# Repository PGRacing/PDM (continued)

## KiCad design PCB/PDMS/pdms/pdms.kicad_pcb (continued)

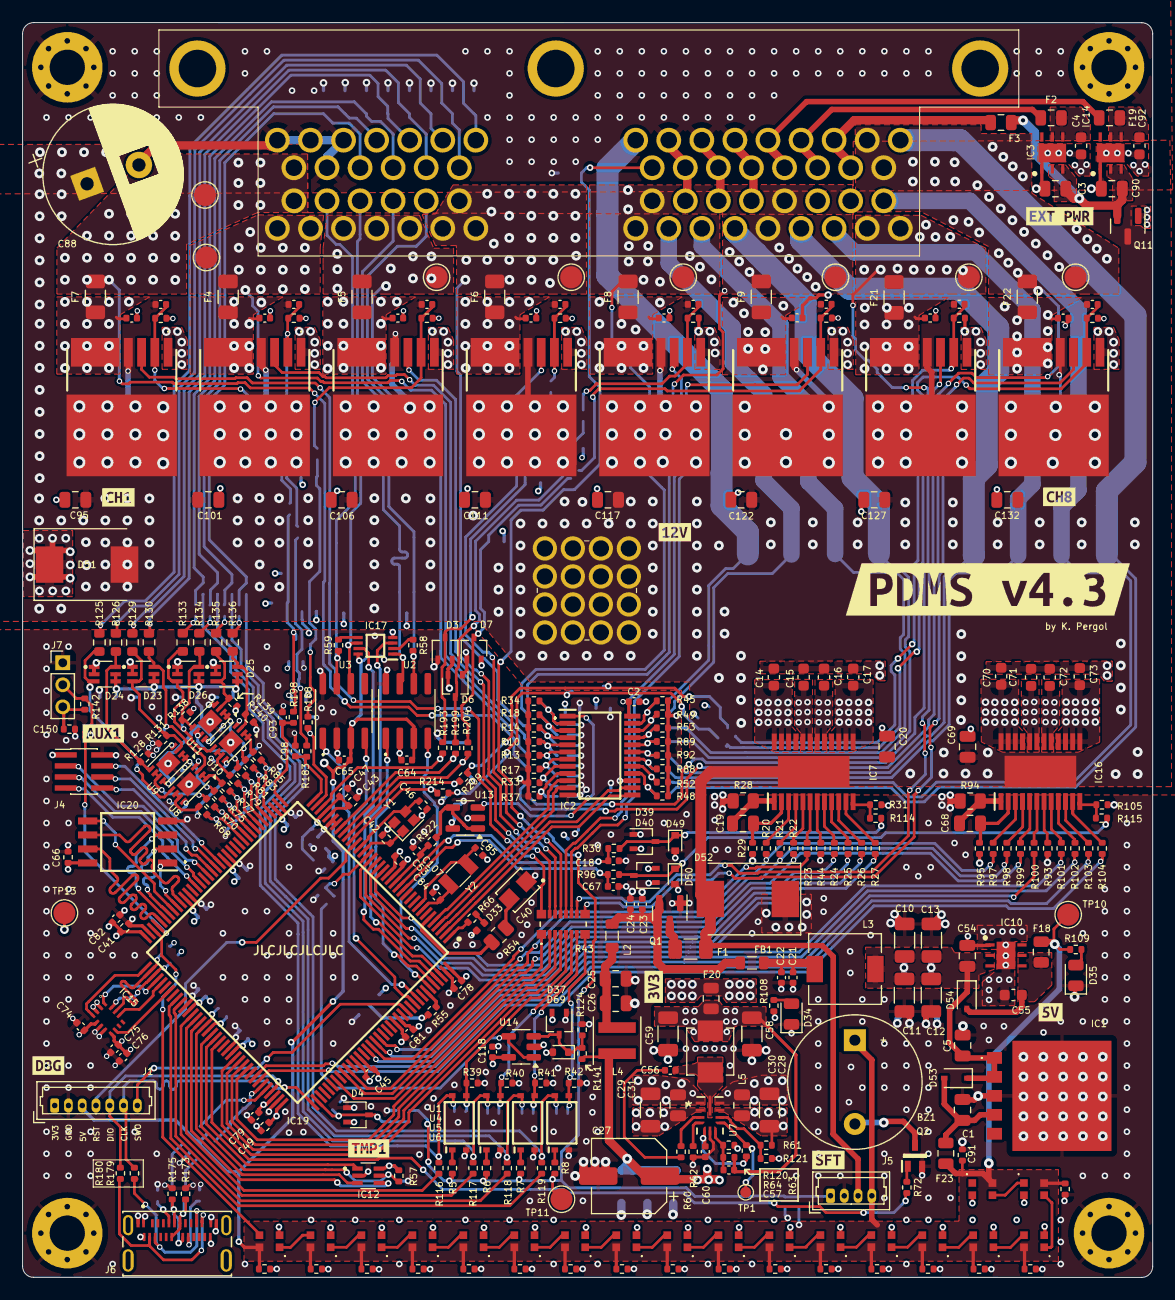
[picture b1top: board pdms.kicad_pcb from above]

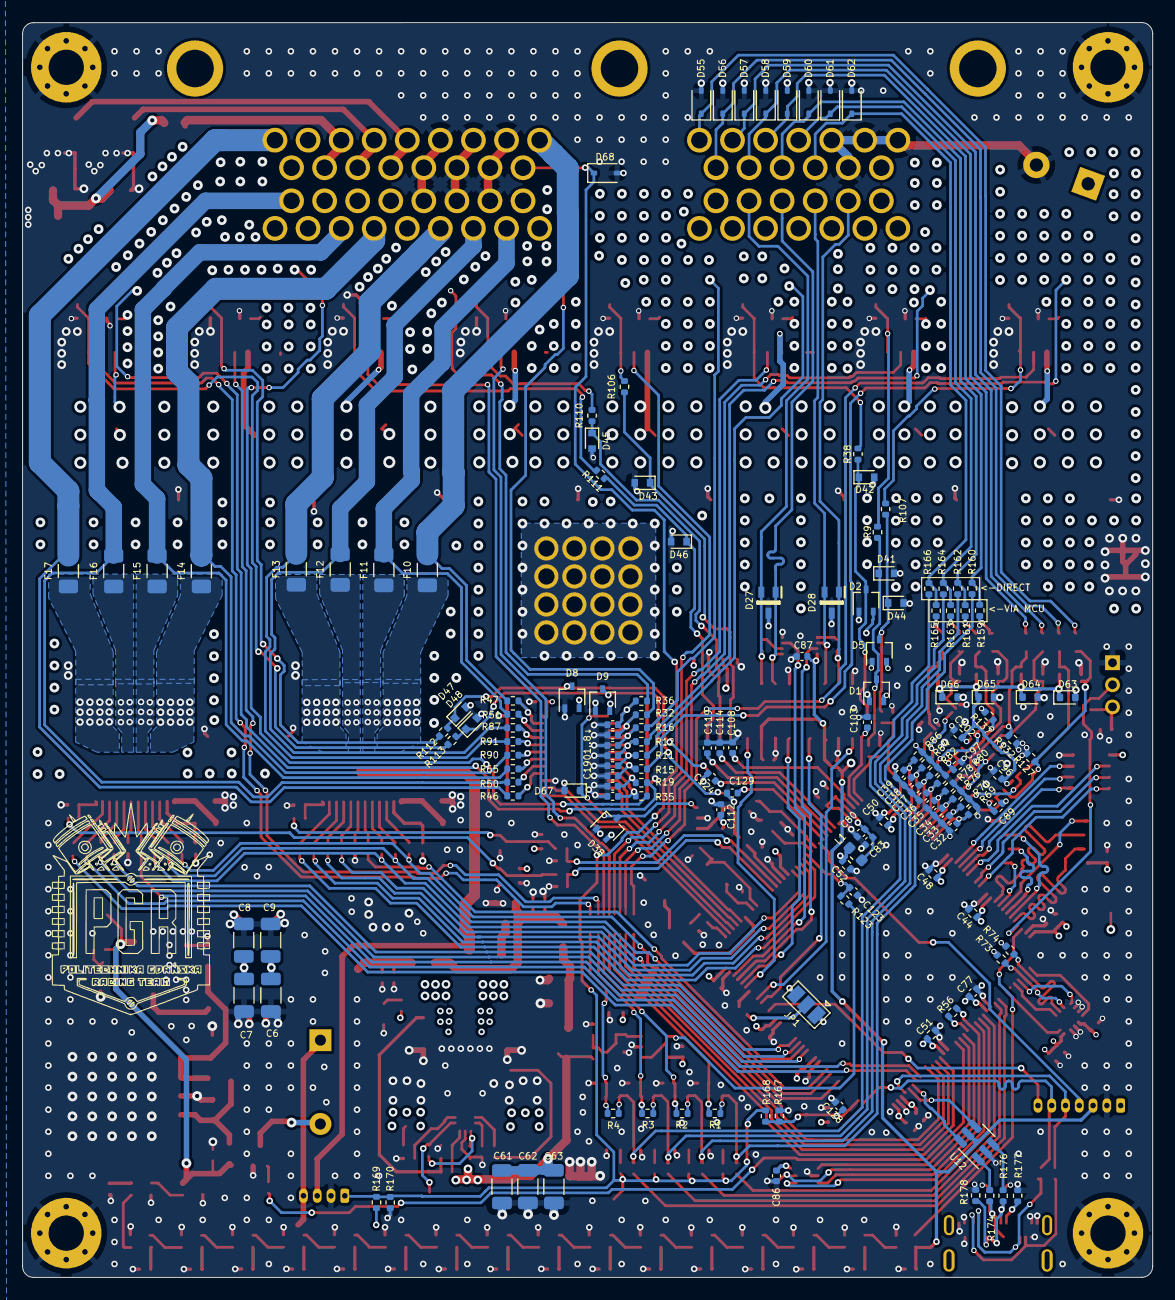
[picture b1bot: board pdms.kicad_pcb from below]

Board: 4 copper layers, 102.5 x 113.8 mm, 509 parts (147 on the bottom side), 300 nets.

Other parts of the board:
Ge: LOGO
kibuzzard-65AD9CDA: G***; kibuzzard-65AD9CDA
kibuzzard-65C2D9B8: G***; kibuzzard-65C2D9B8
kibuzzard-65C96195: G***; kibuzzard-65C96195
kibuzzard-646F7EA8: G***; kibuzzard-646F7EA8
kibuzzard-664CF65B: G***; kibuzzard-664CF65B
kibuzzard-680F5382: G***; kibuzzard-680F5382
kibuzzard-6477C3F8: G***; kibuzzard-6477C3F8
kibuzzard-64698A06: G***; kibuzzard-64698A06
kibuzzard-64713E79: G***; kibuzzard-64713E79
kibuzzard-64714FCB: G***; kibuzzard-64714FCB
kibuzzard-64716719: G***; kibuzzard-64716719

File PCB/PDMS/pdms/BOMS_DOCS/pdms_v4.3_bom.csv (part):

"Reference";"Value";"Datasheet";"Footprint";"Qty";"DNP"
"BZ1";"Buzzer";"~";"Buzzer_Beeper:Buzzer_12x9.5RM7.6";"1";""
"C1,C4,C28,C29,C55,C92";"4.7uF";"~";"-- mixed values --";"6";""
"C2,C20,C44,C45,C47,C48,C49,C50,C51,C52,C53,C64,C65,C66,C69,C74,C76,C77,C78,C79,C80,C81,C82,C86,C87,C89,C91,C95,C96,C97,C101,C102,C106,C111,C112,C117,C118,C122,C127,C132,C133,C134,C135,C136,C137,C138,C139,C140,C141,C142,C143,C144,C145,C146,C147,C148,C149,C150";"100nF";"~";"-- mixed values --";"58";""
"C3,C5,C43,C54,C60,C83,C90";"1uF";"~";"-- mixed values --";"7";""
"C6,C7,C8,C9,C10,C11,C12,C13";"10uF";"~";"Capacitor_SMD:C_1206_3216Metric";"8";""
"C14,C15,C16,C17,C24,C70,C71,C72,C73,C75,C93,C94,C98,C100,C103,C105,C108,C110,C114,C116,C119,C121,C124,C126,C129,C131";"10nF";"~";"-- mixed values --";"26";""
"C18,C67";"220pF";"~";"Capacitor_SMD:C_0402_1005Metric";"2";""
"C19,C68";"470nF";"~";"Capacitor_SMD:C_0805_2012Metric";"2";""
"C21";"100pF/50V";"~";"Capacitor_SMD:C_0402_1005Metric";"1";""
"C22";"100nF/50V";"~";"Capacitor_SMD:C_0402_1005Metric";"1";""
"C23,C99,C104,C109,C113,C115,C120,C125,C130";"1nF";"~";"Capacitor_SMD:C_0402_1005Metric";"9";""
"C25,C26";"2.2uF";"~";"Capacitor_SMD:C_0805_2012Metric";"2";""
"C27,C58,C59";"22uF";"~";"-- mixed values --";"3";""
"C30,C31";"0.1uF";"~";"Capacitor_SMD:C_0805_2012Metric";"2";""
"C32,C33,C34,C35,C36,C37,C38,C39,C56";"47nF";"~";"Capacitor_SMD:C_0402_1005Metric";"9";""
"C40";"1F";"~";"PDMS_Additional:CAPCP3225X100N";"1";""
"C41";"4u7";"~";"Resistor_SMD:R_0402_1005Metric";"1";""
"C42,C46,C57,C84,C85";"10pF";"~";"-- mixed values --";"5";""
"C61,C62";"10uF";"~";"Capacitor_SMD:C_1206_3216Metric";"2";"DNP"
"C63";"2.2uF";"~";"Capacitor_SMD:C_1206_3216Metric";"1";"DNP"
"C88";"1000uF";"~";"Capacitor_THT:CP_Radial_D12.5mm_P5.00mm";"1";""
"C107,C123,C128,R122,R123";"NA";"~";"-- mixed values --";"5";""
"D1,D2,D3,D4,D5,D6,D7,D8,D9,D37,D38,D39,D40";"BAT54SW";"https://assets.nexperia.com/documents/data-sheet/BAT54W_SER.pdf";"Package_TO_SOT_SMD:SOT-323_SC-70";"13";""
"D10,D11,D12,D13,D14,D15,D16,D17,D18,D19,D20,D21,D22,D29,D30,D31,D32,D36";"WS2812B-2020";"";"PDMS_Additional:WS2812B2020";"18";""
"D23,D24,D25,D26";"BAT54BRW-7-F";"";"PDM_Additional:SOT65P210X110-6N";"4";""
"D27,D28";"PESD2CANFD24L-UX";"https://assets.nexperia.com/documents/data-sheet/PESD2CANFD2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";"PDMS_Additional:SOT65P210X110-3N";"2";""
"D33,D34,D35";"LED";"~";"-- mixed values --";"3";""
"D41,D42,D43,D44,D45,D46,D47,D48,D49,D50,D67,D69";"SZMM5Z3V9";"SZMM5Z3V3T1G ";"Diode_SMD:D_SOD-523";"12";""
"D51";"SMC_TVS_28V";"~";"Diode_SMD:D_SMC";"1";""
"D52";"D_TVS";"~";"Diode_SMD:D_SMC";"1";""
"D53,D54";"1N4448WS";"https://www.vishay.com/docs/81387/1n4448ws.pdf";"Diode_SMD:D_SOD-323";"2";""
"D55,D56,D57,D58,D59,D60,D61,D62";"TSD05";"~";"Diode_SMD:D_SOD-323";"8";""
"D63,D64,D65,D66";"SZMM5Z5V3";"~";"Diode_SMD:D_SOD-523";"4";""
"D68";"12V";"~";"Diode_SMD:D_SOD-323";"1";""
"F1,F20";"2A";"~";"-- mixed values --";"2";""
"F2,F18,F19,F23";"100mA";"~";"Fuse:Fuse_0805_2012Metric";"4";""
"F3";"3A";"~";"Fuse:Fuse_0805_2012Metric";"1";""
"F4,F5,F6,F7,F8,F9,F21,F22";"Fuse";"~";"Fuse:Fuse_1206_3216Metric";"8";""
"F10,F11,F12,F13,F14,F15,F16,F17";"7A";"~";"Fuse:Fuse_1206_3216Metric";"8";""
"FB1,L2";"742792063";"~";"Inductor_SMD:L_0805_2012Metric";"2";""
"H1,H2,H3,H4";"MountingHole_Pad";"~";"MountingHole:MountingHole_3.2mm_M3_Pad_Via";"4";""
"IC1";"BD50FD0WHFP-TR";"";"PDMS_Additional:BD50FD0WHFPTR";"1";""
"IC2";"74HC4067PW-Q100J";"";"PDMS_Additional:SOP65P640X110-24N";"1";""
"IC3";"LDO40LPU33RY";"";"PDMS_Additional:SON95P300X300X90-7N-D";"1";""
"IC7,IC16";"BTS722204ESAXUMA1";"https://www.infineon.com/dgdl/Infineon-BTS72220-4ESA-DS-v01_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";"PDMS_Additional:SOP65P600X115-25N";"2";""
"IC10,IC14";"LDO40LPU50RY";"https://componentsearchengine.com/Datasheets/1/LDO40LPU50RY.pdf";"PDMS_Additional:SON95P300X300X90-7N-D";"2";""
"IC12";"TMP126NDCKR";"https://www.ti.com/lit/ds/symlink/tmp126.pdf";"PDM_Additional:SOT65P210X110-6N";"1";""
"IC15";"ASM330LHHTR";"https://www.st.com/resource/en/datasheet/asm330lhh.pdf";"PDMS_Additional:LGA-14_2.5X3X0.86_";"1";""
"IC17";"TS5A21366DCUR";"https://datasheet.datasheetarchive.com/originals/distributor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";"PDM_Additional:SOP50P310X90-8N";"1";""
"IC19";"STM32L496ZGT6";"https://componentsearchengine.com/Datasheets/2/STM32L496ZGT6.pdf";"PDM_Additional:QFP50P2200X2200X160-144N";"1";""
"IC20";"AT25SF128A-SHB-T";"https://www.dialog-semiconductor.com/sites/default/files/202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";"PDM_Additional:SOIC127P798X216-8N";"1";""
"J1";"DBG";"~";"Connector_Molex:Molex_PicoBlade_53047-0710_1x07_P1.25mm_Vertical";"1";""
"J2";"6473427-1";"https://www.te.com/commerce/DocumentDelivery/DDEController?A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";"PDMS_Additional:64734271";"1";""
"J3";"7461383";"";"PDMS_Additional:7461383";"1";""
"J4";"AUX";"~";"Connector_PinHeader_1.00mm:PinHeader_2x04_P1.00mm_Vertical_SMD";"1";""
"J5";"SAFETY";"~";"Connector_Molex:Molex_PicoBlade_53047-0410_1x04_P1.25mm_Vertical";"1";"DNP"
"J6";"2305018-2";"";"PDMS_Additional:TE_2305018-2";"1";""
"J7";"Conn_01x03_Pin";"~";"Connector_PinHeader_2.00mm:PinHeader_1x03_P2.00mm_Vertical";"1";""
"JP1";"SolderJumper_3_Open";"~";"Jumper:SolderJumper-3_P1.3mm_Open_Pad1.0x1.5mm";"1";""
"L1";"2u7 120m";"~";"Inductor_SMD:L_0603_1608Metric";"1";""
"L3";"120uH / 3A";"~";"Inductor_SMD:L_6.3x6.3_H3";"1";""
"L4";"XEL4020-102MEB";"~";"Inductor_SMD:L_Coilcraft_XxL4020";"1";""
"L5";"2.2uH";"~";"Inductor_SMD:L_Vishay_IHLP-1616";"1";""
"Q1";"Si2319CDS";"http://www.aosmd.com/pdfs/datasheet/AO3401A.pdf";"Package_TO_SOT_SMD:SOT-23";"1";""
"Q2";"RJU002N06FRAT106";"https://datasheet.datasheetarchive.com/originals/distributor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";"PDMS_Additional:SOT65P210X110-3N";"1";""
"Q3,Q4,Q5,Q6,Q7,Q8,Q9,Q10";"BTS500101LUAAUMA1";"";"PDM_Additional:BTS500101LUAAUMA1";"8";""
"Q11";"AO3401A";"http://www.aosmd.com/pdfs/datasheet/AO3401A.pdf";"Package_TO_SOT_SMD:SOT-23";"1";""
"R1,R2,R3,R4,R160,R162,R164,R166";"0Ohm";"~";"Resistor_SMD:R_0402_1005Metric";"8";"DNP"
"R5,R6,R7,R8,R55,R67,R72,R185,R190,R195,R201,R206,R211,R216";"1k";"~";"Resistor_SMD:R_0402_1005Metric";"14";""
"R9,R24,R25,R26,R27,R30,R38,R96,R101,R102,R103,R104,R106,R107,R110,R111,R112,R113,R114,R115,R183,R188,R193,R198,R199,R204,R209,R214";"4.7k";"~";"Resistor_SMD:R_0402_1005Metric";"28";""
"R10,R13,R14,R17,R18,R33,R34,R37,R45,R48,R49,R52,R53,R88,R89,R92";"2.3k";"~";"Resistor_SMD:R_0402_1005Metric";"16";""
"R11,R12,R15,R16,R19,R32,R35,R36,R39,R40,R41,R42,R46,R47,R50,R51,R56,R57,R65,R73,R74,R87,R90,R91,R141,R170";"10k";"~";"Resistor_SMD:R_0402_1005Metric";"26";""
"R20,R21,R22,R23,R31,R44,R68,R70,R75,R77,R79,R81,R83,R85,R93,R97,R98,R99,R100,R105,R168";"1.2k";"~";"Resistor_SMD:R_0402_1005Metric";"21";""
"R28,R94";"47";"~";"Resistor_SMD:R_0805_2012Metric";"2";""
"R29,R95";"470";"~";"Resistor_SMD:R_0402_1005Metric";"2";""
"R43";"EXB-2HV472JV";"EXB-2HV472JV";"PDMS_Additional:RES_EXB2HV";"1";""
"R54,R179,R180";"0";"~";"-- mixed values --";"3";""
"R58,R59";"120";"~";"Resistor_SMD:R_0402_1005Metric";"2";""
"R60";"0R0";"~";"Resistor_SMD:R_0402_1005Metric";"1";""
"R61,R63,R64,R127,R128,R131,R132,R137,R138,R139,R140";"100k";"~";"Resistor_SMD:R_0402_1005Metric";"11";""
"R62";"15k";"~";"Resistor_SMD:R_0402_1005Metric";"1";""
"R66,R108,R109,R173,R175";"1k5";"~";"Resistor_SMD:R_0402_1005Metric";"5";""
"R69,R71,R76,R78,R80,R82,R84,R86,R167";"2.2k";"~";"Resistor_SMD:R_0402_1005Metric";"9";""
"R116,R117,R118,R119,R159,R161,R163,R165";"0Ohm";"~";"Resistor_SMD:R_0402_1005Metric";"8";""
"R120";"31.6k";"~";"Resistor_SMD:R_0402_1005Metric";"1";""
"R121";"NA";"~";"Resistor_SMD:R_0402_1005Metric";"1";"DNP"
"R124";"2.32k";"~";"Resistor_SMD:R_0402_1005Metric";"1";""
"R125,R126,R129,R130,R133,R134,R135,R136";"1k/0.2W";"~";"Resistor_SMD:R_0603_1608Metric";"8";""
"R142";"4k7";"~";"Resistor_SMD:R_0402_1005Metric";"1";""
"R169";"10k";"~";"Resistor_SMD:R_0402_1005Metric";"1";"DNP"
"R174,R176";"22";"~";"Resistor_SMD:R_0402_1005Metric";"2";""
"R177,R178";"5.1k";"~";"Resistor_SMD:R_0402_1005Metric";"2";""
"TP1";"3.3V PG";"~";"TestPoint:TestPoint_Pad_D1.0mm";"1";""
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
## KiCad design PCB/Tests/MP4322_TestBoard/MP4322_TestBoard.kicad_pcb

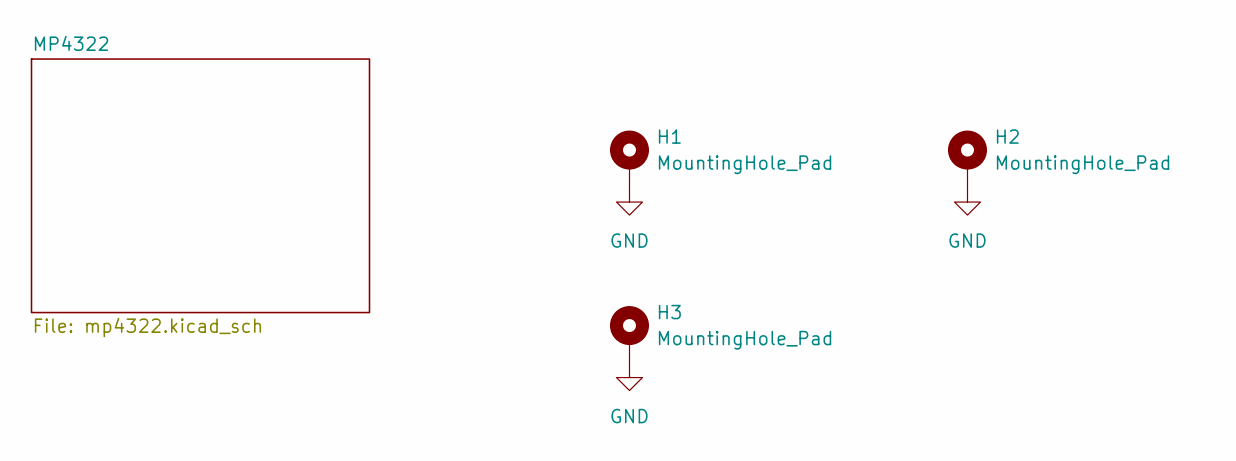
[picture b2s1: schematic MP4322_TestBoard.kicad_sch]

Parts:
H1, H2, H3: MountingHole_Pad; MountingHole_2.2mm_M2_ISO7380_Pad_TopBottom

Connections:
GND: H1.1, H2.1, H3.1; also elsewhere on the board

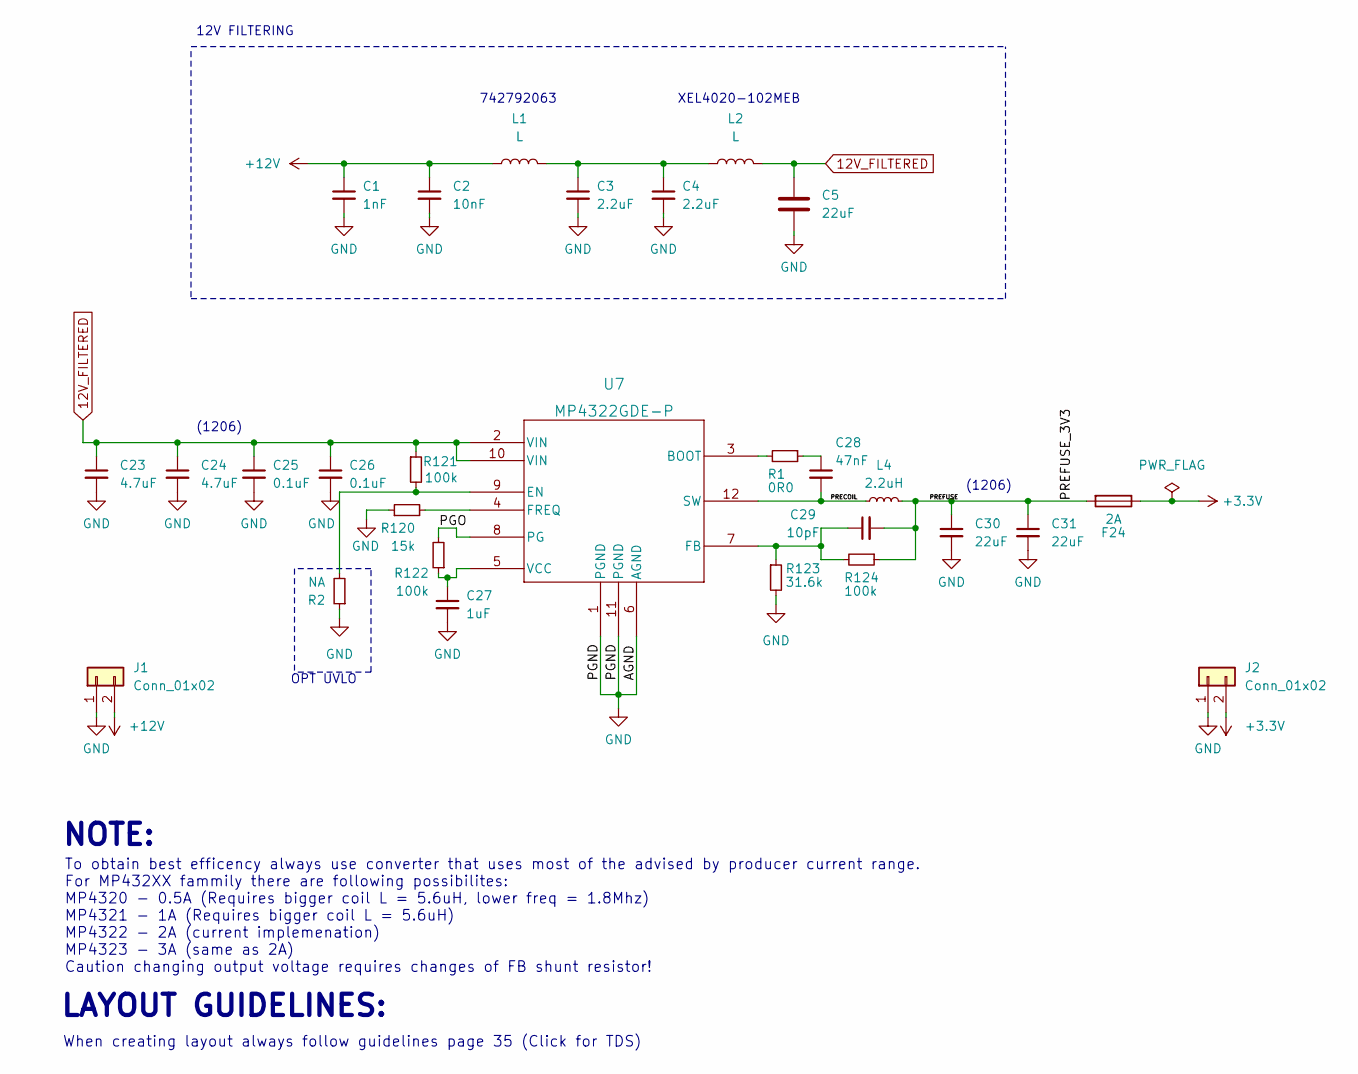
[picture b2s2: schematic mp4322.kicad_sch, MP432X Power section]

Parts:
C1: 1nF; C_0402_1005Metric
C2: 10nF; C_0402_1005Metric
C3, C4: 2.2uF; C_0805_2012Metric
C5: 22uF; CP_Elec_6.3x9.9
C23, C24: 4.7uF; C_1206_3216Metric
C25, C26: 0.1uF; C_0805_2012Metric
C27: 1uF; C_0402_1005Metric
C28: 47nF; C_0402_1005Metric
C29: 10pF; C_0402_1005Metric
C30, C31: 22uF; C_1206_3216Metric
F24: 2A; Fuse_0805_2012Metric
J1, J2: Conn_01x02; JST_EH_B2B-EH-A_1x02_P2.50mm_Vertical
L1: L; L_0805_2012Metric
L2: L; L_Coilcraft_XxL4020
L4: 2.2uH; L_Vishay_IHLP-1616
R1: 0R0; R_0402_1005Metric
R2: NA; R_0402_1005Metric
R120: 15k; R_0402_1005Metric
R121, R122, R124: 100k; R_0402_1005Metric
R123: 31.6k; R_0402_1005Metric
U7: MP4322GDE-P; QFN-12_MP4322_MNP

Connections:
12V_FILTERED: C5.1, C23.1, C24.1, C25.1, C26.1, L2.1, R121.1, U7.2 (VIN), U7.10 (VIN)
+3.3V: F24.1, J2.2
+12V: C1.1, C2.1, J1.2, L1.1
/MP4322/PGO: R122.2, U7.8 (PG)
/MP4322/PRECOIL: C28.2, L4.1, U7.12 (SW)
/MP4322/PREFUSE: C29.2, C30.1, C31.1, F24.2, L4.2, R124.1
GND: C1.2, C2.2, C3.2, C4.2, C5.2, C23.2, C24.2, C25.2, C26.2, C27.2, C30.2, C31.2, J1.1, J2.1, R2.1, R120.1, R123.2, U7.1 (PGND), U7.6 (AGND), U7.11 (PGND); also elsewhere on the board
unnamed: C3.1, C4.1, L1.2, L2.2
unnamed: C27.1, R122.1, U7.5 (VCC)
unnamed: C28.1, R1.1
unnamed: C29.1, R123.1, R124.2, U7.7 (FB)
unnamed: R1.2, U7.3 (BOOT)
unnamed: R120.2, U7.4 (FREQ)
unnamed: R2.2, R121.2, U7.9 (EN)

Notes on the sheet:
(1206)
12V FILTERING
XEL4020-102MEB
When creating layout always follow guidelines page 35 (Click for TDS)
742792063
To obtain best efficency always use converter that uses most of the advised by producer current range. For MP432XX fammily there are following possibilites: MP4320 - 0.5A (Requires bigger coil L = 5.6uH, lower freq = 1.8Mhz) MP4321 - 1A (Requires bigger coil L = 5.6uH) MP4322 - 2A (current implemen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
(1206)
LAYOUT GUIDELINES:
NOTE:
OPT UVLO

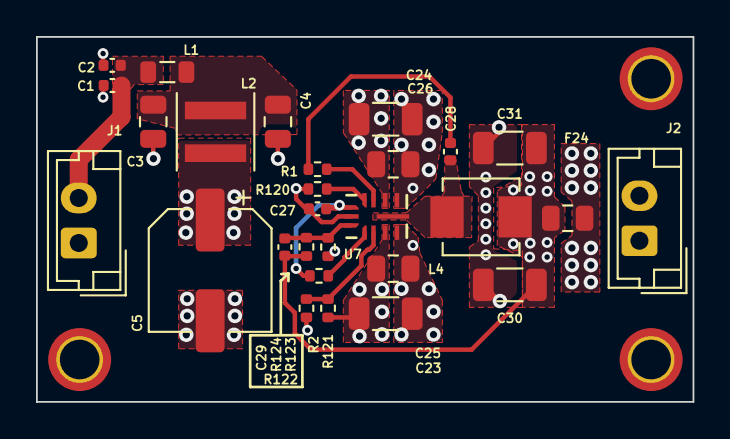
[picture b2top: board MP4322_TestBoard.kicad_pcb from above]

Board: 4 copper layers, 36.5 x 20.3 mm, 31 parts (0 on the bottom side), 14 nets.

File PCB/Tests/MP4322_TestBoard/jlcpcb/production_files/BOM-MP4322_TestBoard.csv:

Comment,Designator,Footprint,LCSC
22uF,"C30,C31",C_1206_3216Metric,C12891
10nF,C2,C_0402_1005Metric,C15195
1nF,C1,C_0402_1005Metric,C1523
L,L2,L_Coilcraft_XxL4020,C19191618
L,L1,L_0805_2012Metric,C2661451
4.7uF,"C23,C24",C_1206_3216Metric,C29823
10pF,C29,C_0402_1005Metric,C32949
2.2uF,"C3,C4",C_0805_2012Metric,C377773
0.1uF,"C25,C26",C_0805_2012Metric,C49678
1uF,C27,C_0402_1005Metric,C52923
2.2uH,L4,L_Vishay_IHLP-1616,C844979
0R0,R1,R_0402_1005Metric,
15k,R120,R_0402_1005Metric,
22uF,C5,CP_Elec_6.3x9.9,
100k,R122,R_0402_1005Metric,
31.6k,R123,R_0402_1005Metric,
100k,R124,R_0402_1005Metric,
47nF,C28,C_0402_1005Metric,
100k,R121,R_0402_1005Metric,
NA,R2,R_0402_1005Metric,
2A,F24,Fuse_0805_2012Metric,

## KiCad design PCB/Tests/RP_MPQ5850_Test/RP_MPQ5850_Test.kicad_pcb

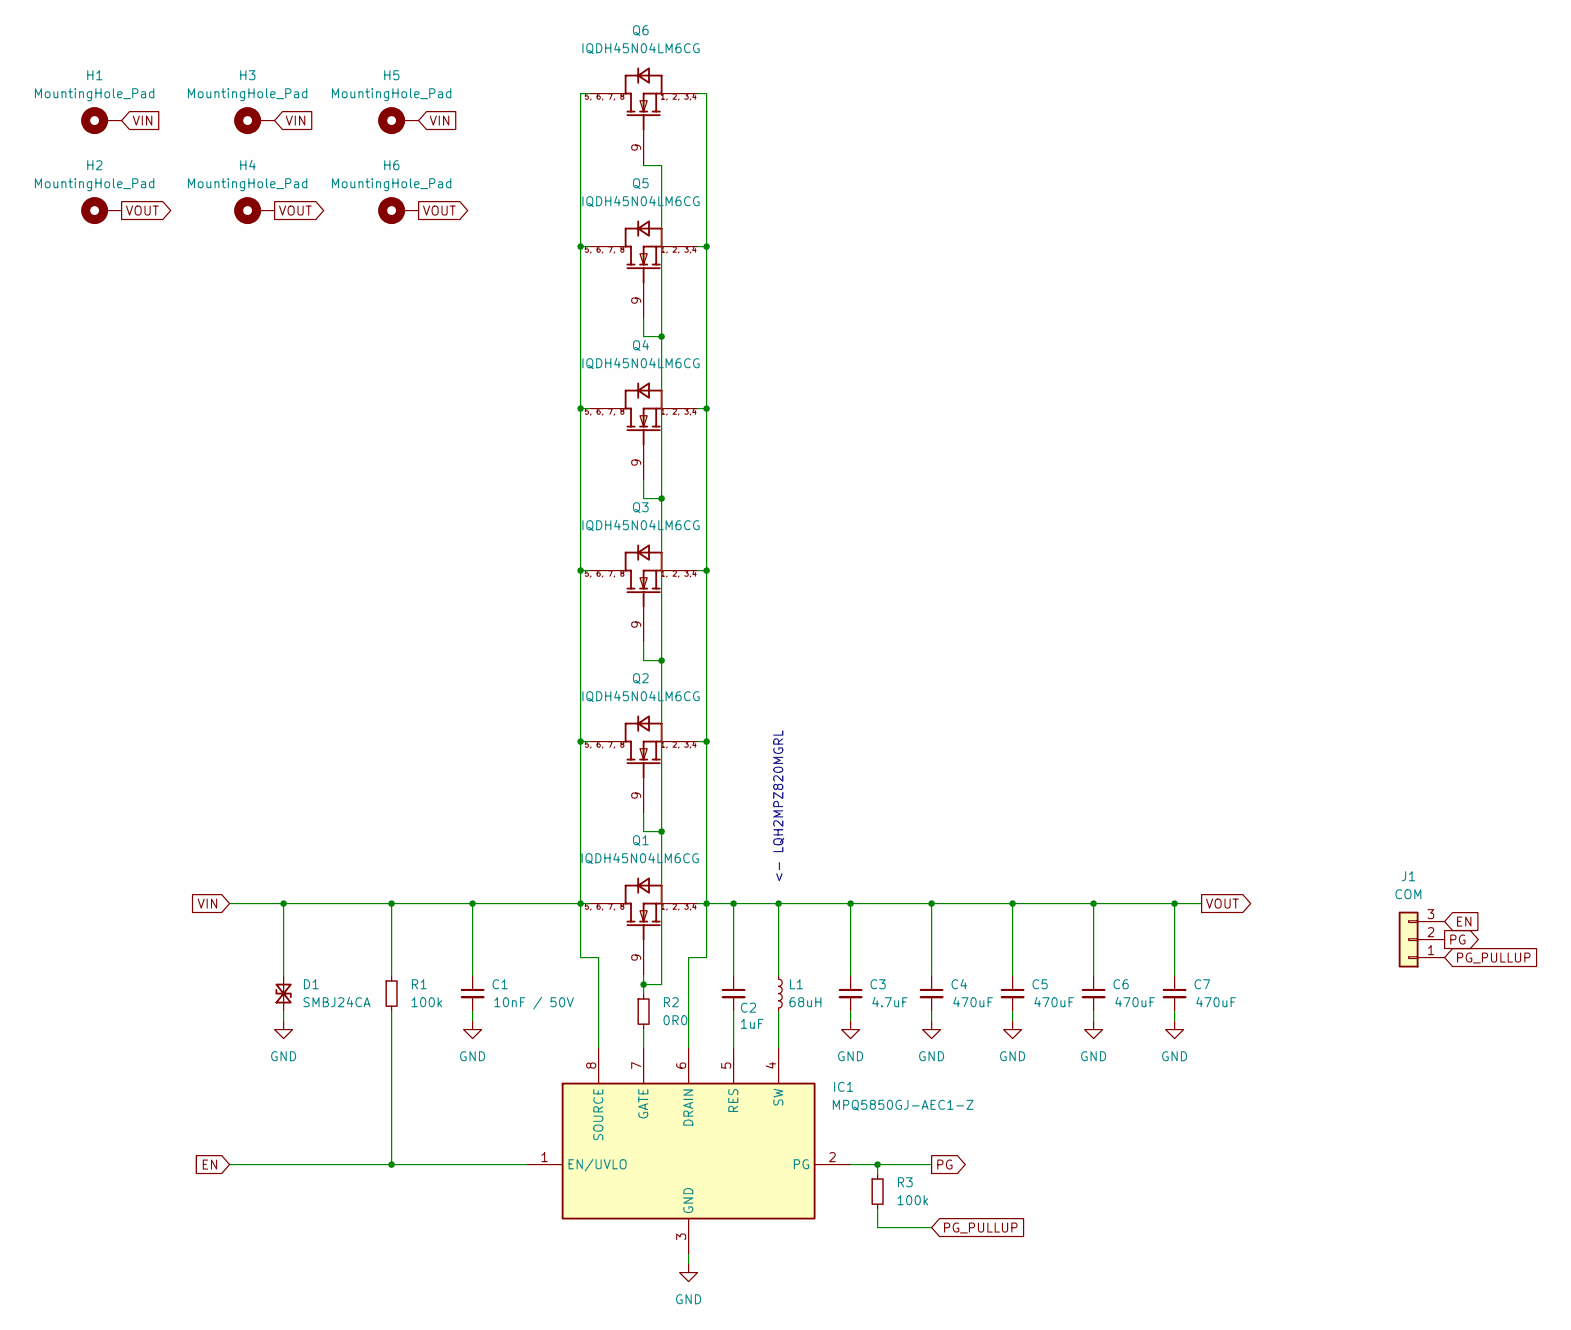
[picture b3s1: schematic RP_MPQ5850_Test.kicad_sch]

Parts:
C1: 10nF / 50V; D_0603_1608Metric
C2: 1uF; D_0805_2012Metric
C3: 4.7uF; D_1206_3216Metric
C4, C5, C6, C7: 470uF; CP_Radial_D12.5mm_P5.00mm
D1: SMBJ24CA; D_SMB
H1, H2, H3, H4, H5, H6: MountingHole_Pad; MountingHole_6mm_Pad_TopBottom
IC1: MPQ5850GJ-AEC1-Z; SOT65P280X100-8N; Manufacturer_Part_Number MPQ5850GJ-AEC1-Z
J1: COM; PinHeader_1x03_P2.54mm_Vertical
L1: 68uH; LQH2MCN100K02L
Q1, Q2, Q3, Q4, Q5, Q6: IQDH45N04LM6CG; IFX-PG-TTFN-9-2-V
R1, R3: 100k; R_0402_1005Metric
R2: 0R0; R_0402_1005Metric

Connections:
EN: IC1.1 (EN/UVLO), J1.3, R1.2
GND: C1.2, C3.2, C4.2, C5.2, C6.2, C7.2, D1.1 (A1), IC1.3 (GND)
unnamed: IC1.7 (GATE), R2.2
unnamed: C2.2, IC1.5 (RES)
unnamed: IC1.4 (SW), L1.2
unnamed: Q1.9 (GATE), Q2.9 (GATE), Q3.9 (GATE), Q4.9 (GATE), Q5.9 (GATE), Q6.9 (GATE), R2.1
PG: IC1.2 (PG), J1.2, R3.1
PG_PULLUP: J1.1, R3.2
VIN: C1.1, D1.2 (A2), H1.1, H3.1, H5.1, IC1.8 (SOURCE), Q1.5 (DRAIN1), Q1.6 (DRAIN2), Q1.7 (DRAIN3), Q1.8 (DRAIN4), Q2.5 (DRAIN1), Q2.6 (DRAIN2), Q2.7 (DRAIN3), Q2.8 (DRAIN4), Q3.5 (DRAIN1), Q3.6 (DRAIN2), Q3.7 (DRAIN3), Q3.8 (DRAIN4), Q4.5 (DRAIN1), Q4.6 (DRAIN2), Q4.7 (DRAIN3), Q4.8 (DRAIN4), Q5.5 (DRAIN1), Q5.6 (DRAIN2), Q5.7 (DRAIN3), Q5.8 (DRAIN4), Q6.5 (DRAIN1), Q6.6 (DRAIN2), Q6.7 (DRAIN3), Q6.8 (DRAIN4), R1.1
VOUT: C2.1, C3.1, C4.1, C5.1, C6.1, C7.1, H2.1, H4.1, H6.1, IC1.6 (DRAIN), L1.1, Q1.1 (SOURCE1), Q1.2 (SOURCE2), Q1.3 (SOURCE3), Q1.4 (SOURCE4), Q2.1 (SOURCE1), Q2.2 (SOURCE2), Q2.3 (SOURCE3), Q2.4 (SOURCE4), Q3.1 (SOURCE1), Q3.2 (SOURCE2), Q3.3 (SOURCE3), Q3.4 (SOURCE4), Q4.1 (SOURCE1), Q4.2 (SOURCE2), Q4.3 (SOURCE3), Q4.4 (SOURCE4), Q5.1 (SOURCE1), Q5.2 (SOURCE2), Q5.3 (SOURCE3), Q5.4 (SOURCE4), Q6.1 (SOURCE1), Q6.2 (SOURCE2), Q6.3 (SOURCE3), Q6.4 (SOURCE4)

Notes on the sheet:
<- LQH2MPZ820MGRL

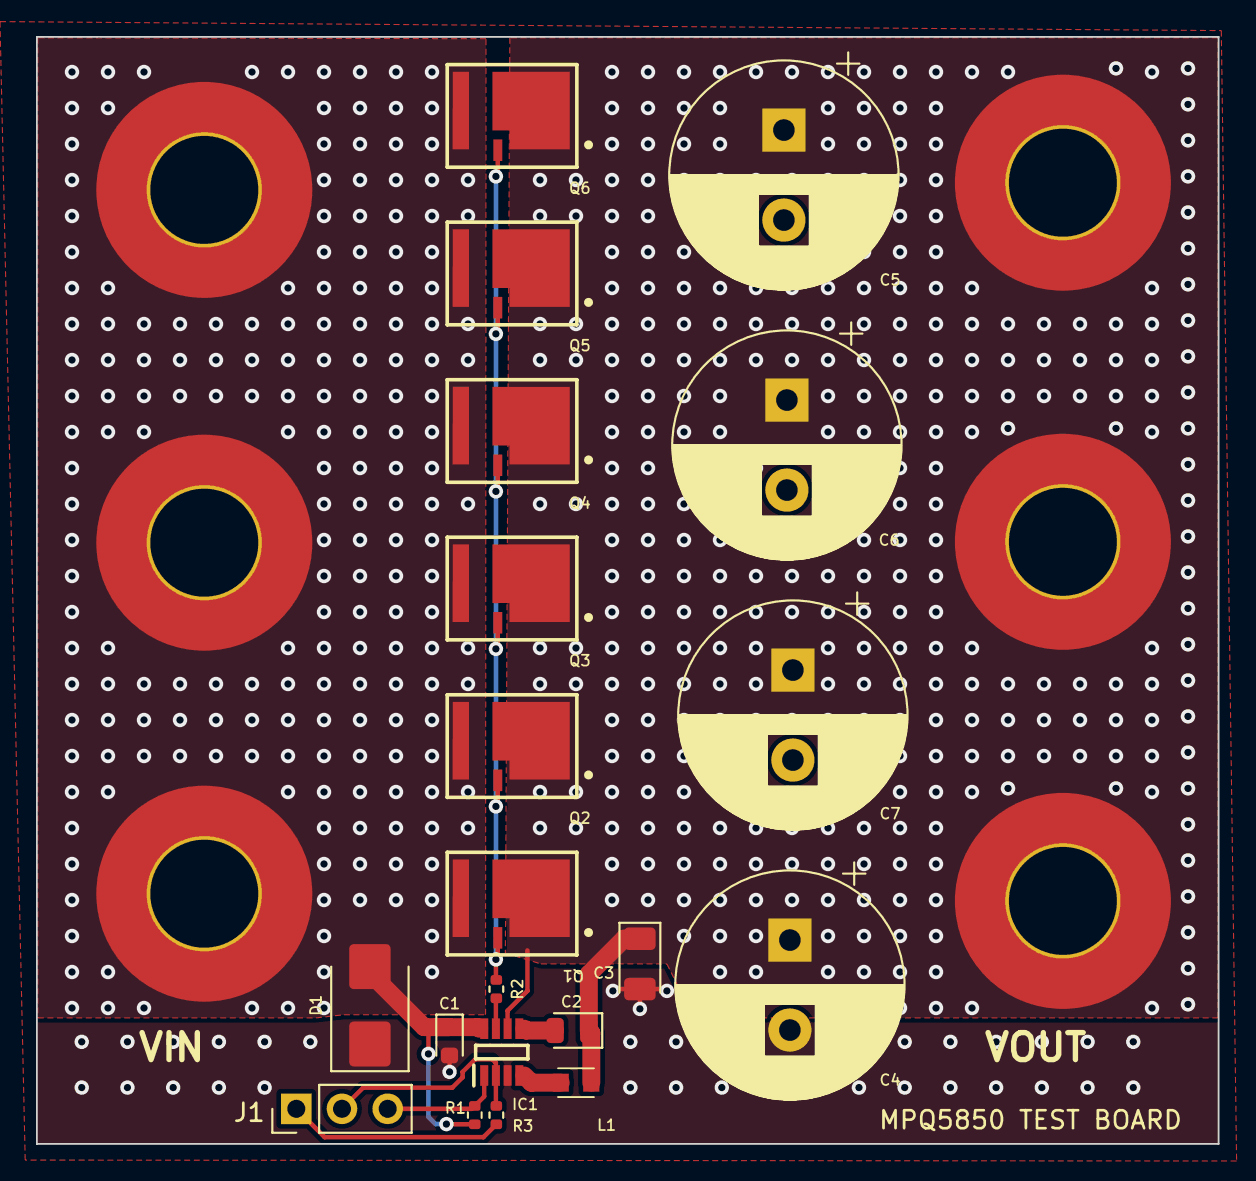
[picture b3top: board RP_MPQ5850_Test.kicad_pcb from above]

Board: 4 copper layers, 65.7 x 61.5 mm, 26 parts (0 on the bottom side), 10 nets.

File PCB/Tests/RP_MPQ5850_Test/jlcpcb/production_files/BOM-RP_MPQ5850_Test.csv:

Comment,Designator,Footprint,LCSC,Quantity
IQDH45N04LM6CG,Q3,IFX-PG-TTFN-9-2-V,,1
0R0,R2,R_0402_1005Metric,,1
4.7uF,C3,D_1206_3216Metric,,1
MPQ5850GJ-AEC1-Z,IC1,SOT65P280X100-8N,,1
COM,J1,PinHeader_1x03_P2.54mm_Vertical,,1
IQDH45N04LM6CG,Q1,IFX-PG-TTFN-9-2-V,,1
IQDH45N04LM6CG,Q5,IFX-PG-TTFN-9-2-V,,1
470uF,C7,CP_Radial_D12.5mm_P5.00mm,,1
SMBJ24CA,D1,D_SMB,,1
10nF / 50V,C1,D_0603_1608Metric,,1
1uF,C2,D_0805_2012Metric,,1
IQDH45N04LM6CG,Q4,IFX-PG-TTFN-9-2-V,,1
68uH,L1,LQH2MCN100K02L,,1
100k,R1,R_0402_1005Metric,,1
470uF,C5,CP_Radial_D12.5mm_P5.00mm,,1
IQDH45N04LM6CG,Q2,IFX-PG-TTFN-9-2-V,,1
IQDH45N04LM6CG,Q6,IFX-PG-TTFN-9-2-V,,1
470uF,C6,CP_Radial_D12.5mm_P5.00mm,,1
100k,R3,R_0402_1005Metric,,1
470uF,C4,CP_Radial_D12.5mm_P5.00mm,,1

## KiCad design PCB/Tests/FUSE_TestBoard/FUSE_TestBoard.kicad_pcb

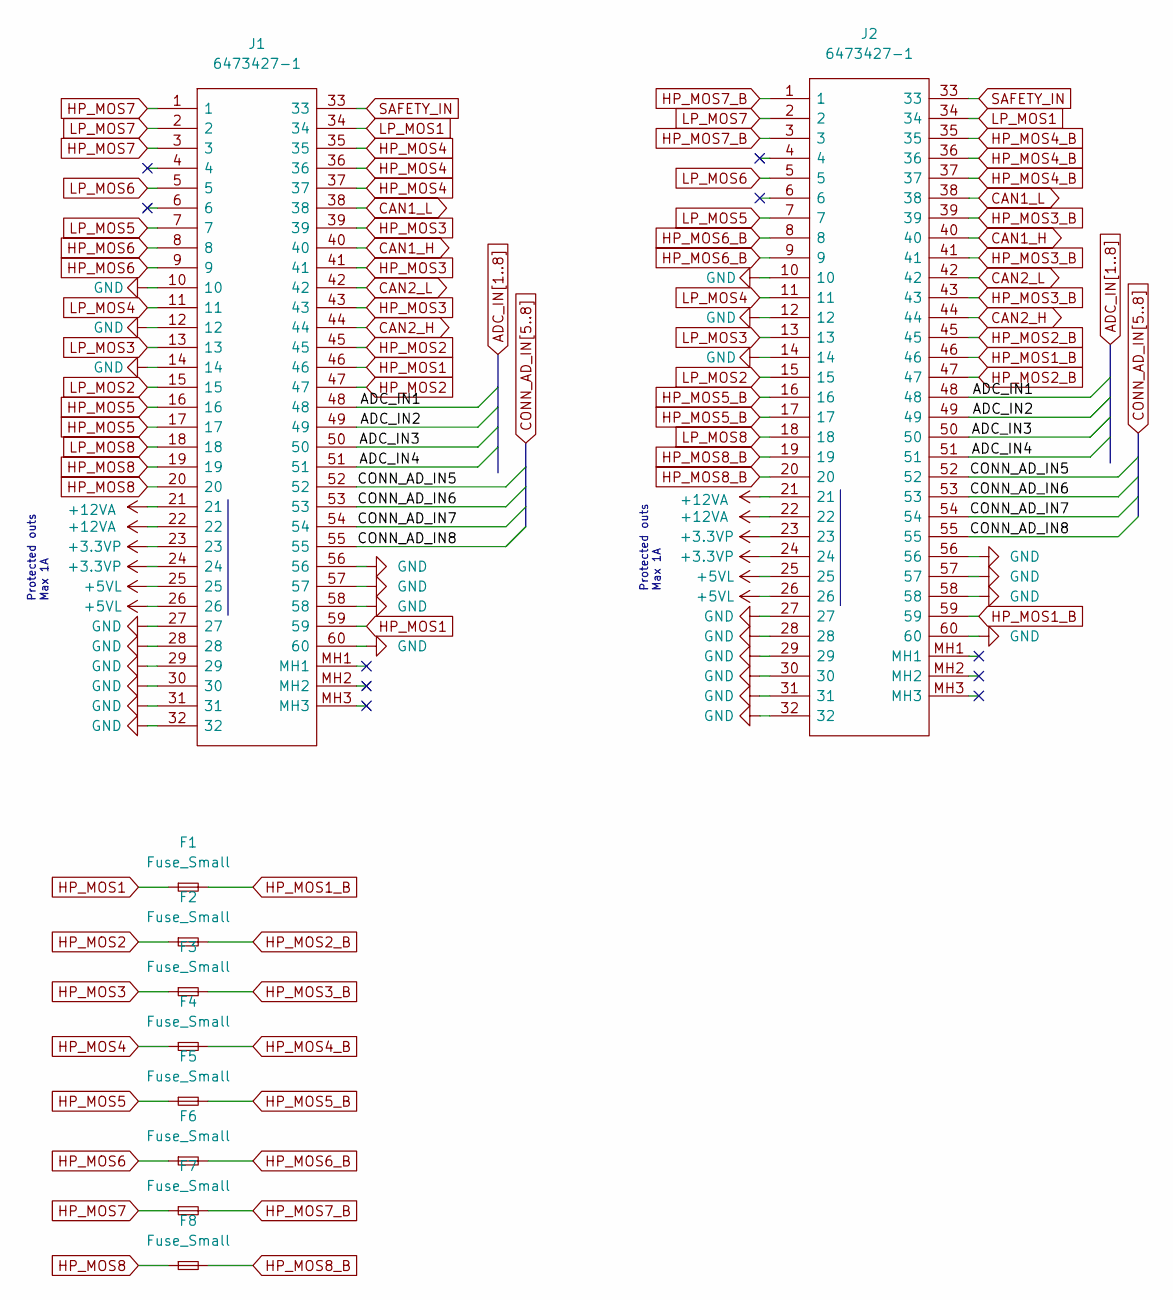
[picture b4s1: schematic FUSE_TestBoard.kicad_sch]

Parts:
F1, F2, F3, F4, F5, F6, F7, F8: Fuse_Small; Fuse_1206_3216Metric_Pad1.42x1.75mm_HandSolder
J1, J2: 6473427-1; 64734271; Manufacturer_Part_Number 6473427-1; Mouser Part Number 571-6473427-1

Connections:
+3.3VP: J1.23, J1.24, J2.23, J2.24
+5VL: J1.25, J1.26, J2.25, J2.26
+12VA: J1.21, J1.22, J2.21, J2.22
ADC_IN1: J1.48, J2.48
ADC_IN2: J1.49, J2.49
ADC_IN3: J1.50, J2.50
ADC_IN4: J1.51, J2.51
CAN1_H: J1.40, J2.40
CAN1_L: J1.38, J2.38
CAN2_H: J1.44, J2.44
CAN2_L: J1.42, J2.42
CONN_AD_IN5: J1.52, J2.52
CONN_AD_IN6: J1.53, J2.53
CONN_AD_IN7: J1.54, J2.54
CONN_AD_IN8: J1.55, J2.55
GND: J1.10, J1.12, J1.14, J1.27, J1.28, J1.29, J1.30, J1.31, J1.32, J1.56, J1.57, J1.58, J1.60, J2.10, J2.12, J2.14, J2.27, J2.28, J2.29, J2.30, J2.31, J2.32, J2.56, J2.57, J2.58, J2.60
HP_MOS1: F1.1, J1.46, J1.59
HP_MOS1_B: F1.2, J2.46, J2.59
HP_MOS2: F2.1, J1.45, J1.47
HP_MOS2_B: F2.2, J2.45, J2.47
HP_MOS3: F3.1, J1.39, J1.41, J1.43
HP_MOS3_B: F3.2, J2.39, J2.41, J2.43
HP_MOS4: F4.1, J1.35, J1.36, J1.37
HP_MOS4_B: F4.2, J2.35, J2.36, J2.37
HP_MOS5: F5.1, J1.16, J1.17
HP_MOS5_B: F5.2, J2.16, J2.17
HP_MOS6: F6.1, J1.8, J1.9
HP_MOS6_B: F6.2, J2.8, J2.9
HP_MOS7: F7.1, J1.1, J1.3
HP_MOS7_B: F7.2, J2.1, J2.3
HP_MOS8: F8.1, J1.19, J1.20
HP_MOS8_B: F8.2, J2.19, J2.20
LP_MOS1: J1.34, J2.34
LP_MOS2: J1.15, J2.15
LP_MOS3: J1.13, J2.13
LP_MOS4: J1.11, J2.11
LP_MOS5: J1.7, J2.7
LP_MOS6: J1.5, J2.5
LP_MOS7: J1.2, J2.2
LP_MOS8: J1.18, J2.18
SAFETY_IN: J1.33, J2.33

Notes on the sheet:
Protected outs Max 1A

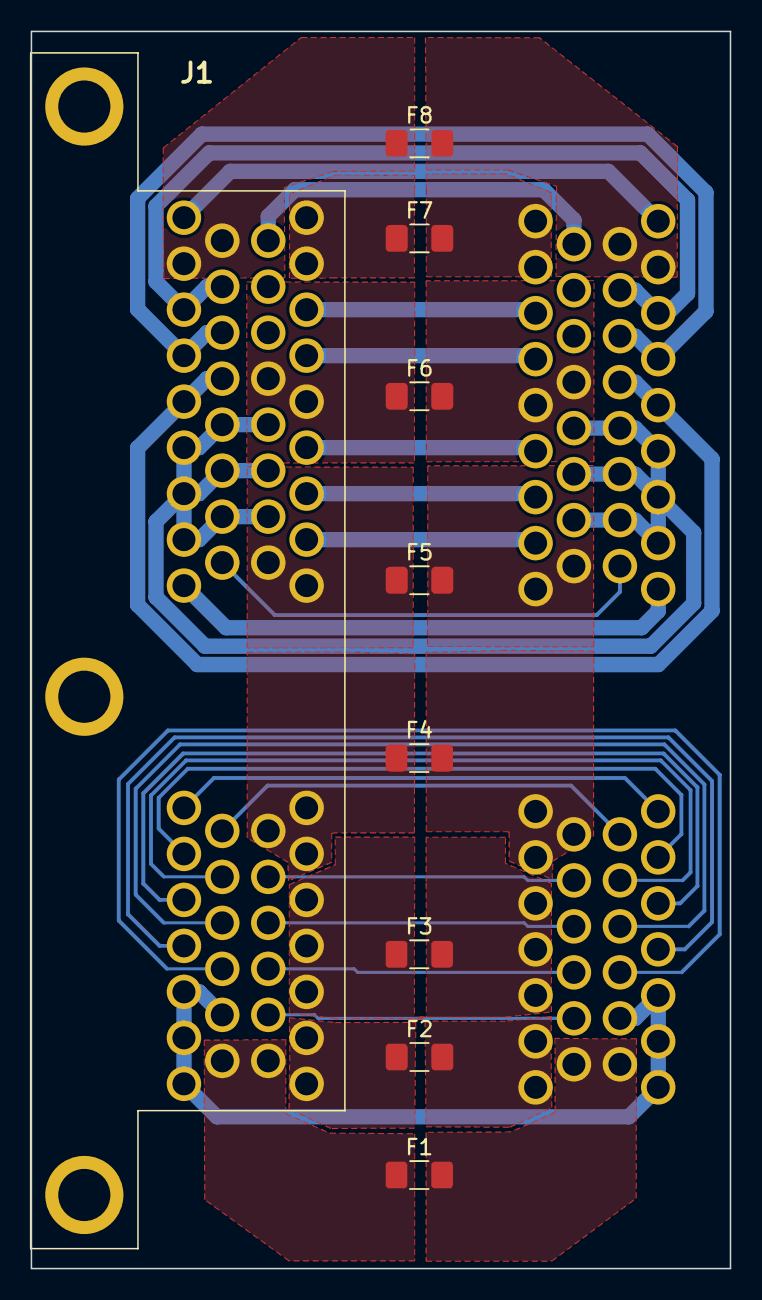
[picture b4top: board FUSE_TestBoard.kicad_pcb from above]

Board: 2 copper layers, 45.6 x 80.7 mm, 10 parts (1 on the bottom side), 41 nets.

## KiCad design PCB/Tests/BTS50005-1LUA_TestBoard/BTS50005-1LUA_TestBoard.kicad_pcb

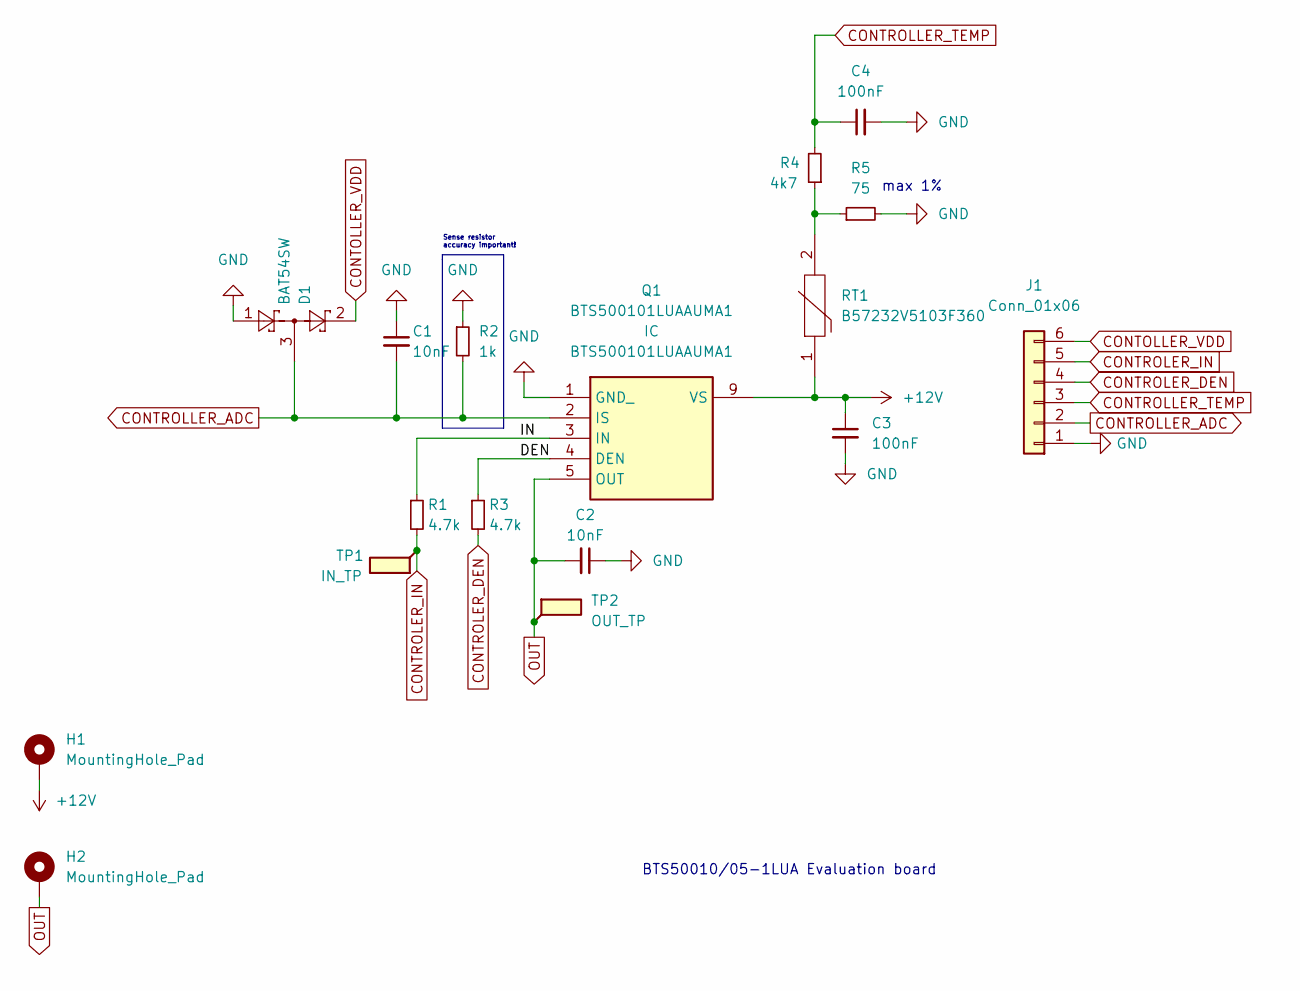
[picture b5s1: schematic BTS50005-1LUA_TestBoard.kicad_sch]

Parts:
C1, C2: 10nF; C_0402_1005Metric
C3: 100nF; C_0805_2012Metric
C4: 100nF; C_0402_1005Metric
D1: BAT54SW; SOT-323_SC-70
H1, H2: MountingHole_Pad; MountingHole_6.5mm_Pad_Via
J1: Conn_01x06; Molex_Micro-Latch_53253-0670_1x06_P2.00mm_Vertical
Q1: BTS500101LUAAUMA1; Manufacturer_Part_Number BTS500101LUAAUMA1; Mouser Part Number 726-BTS500101LUAAUMA
R1, R3: 4.7k; R_0402_1005Metric
R2: 1k; R_0402_1005Metric
R4: 4k7; R_0402_1005Metric
R5: 75; R_0402_1005Metric
RT1: B57232V5103F360; THRMC1005X60N; Manufacturer_Part_Number B57232V5103F360; Mouser Part Number 871-B57232V5103F360
TP1: IN_TP; TestPoint_Keystone_5000-5004_Miniature
TP2: OUT_TP; TestPoint_Keystone_5000-5004_Miniature

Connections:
+12V: C3.1, H1.1, Q1.9 (VS), RT1.1
/DEN: Q1.4 (DEN), R3.1
/IN: Q1.3 (IN), R1.1
CONTOLLER_VDD: D1.2, J1.6
CONTROLER_DEN: J1.4, R3.2
CONTROLER_IN: J1.5, R1.2, TP1.1
CONTROLLER_ADC: C1.2, D1.3, J1.2, Q1.2 (IS), R2.2
CONTROLLER_TEMP: C4.1, J1.3, R4.2
GND: C1.1, C2.1, C3.2, C4.2, D1.1, J1.1, Q1.1 (GND_), R2.1, R5.2
unnamed: R4.1, R5.1, RT1.2
OUT: C2.2, H2.1, Q1.5 (OUT), TP2.1

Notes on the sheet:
BTS50010/05-1LUA Evaluation board
max 1%
Sense resistor accuracy important!
